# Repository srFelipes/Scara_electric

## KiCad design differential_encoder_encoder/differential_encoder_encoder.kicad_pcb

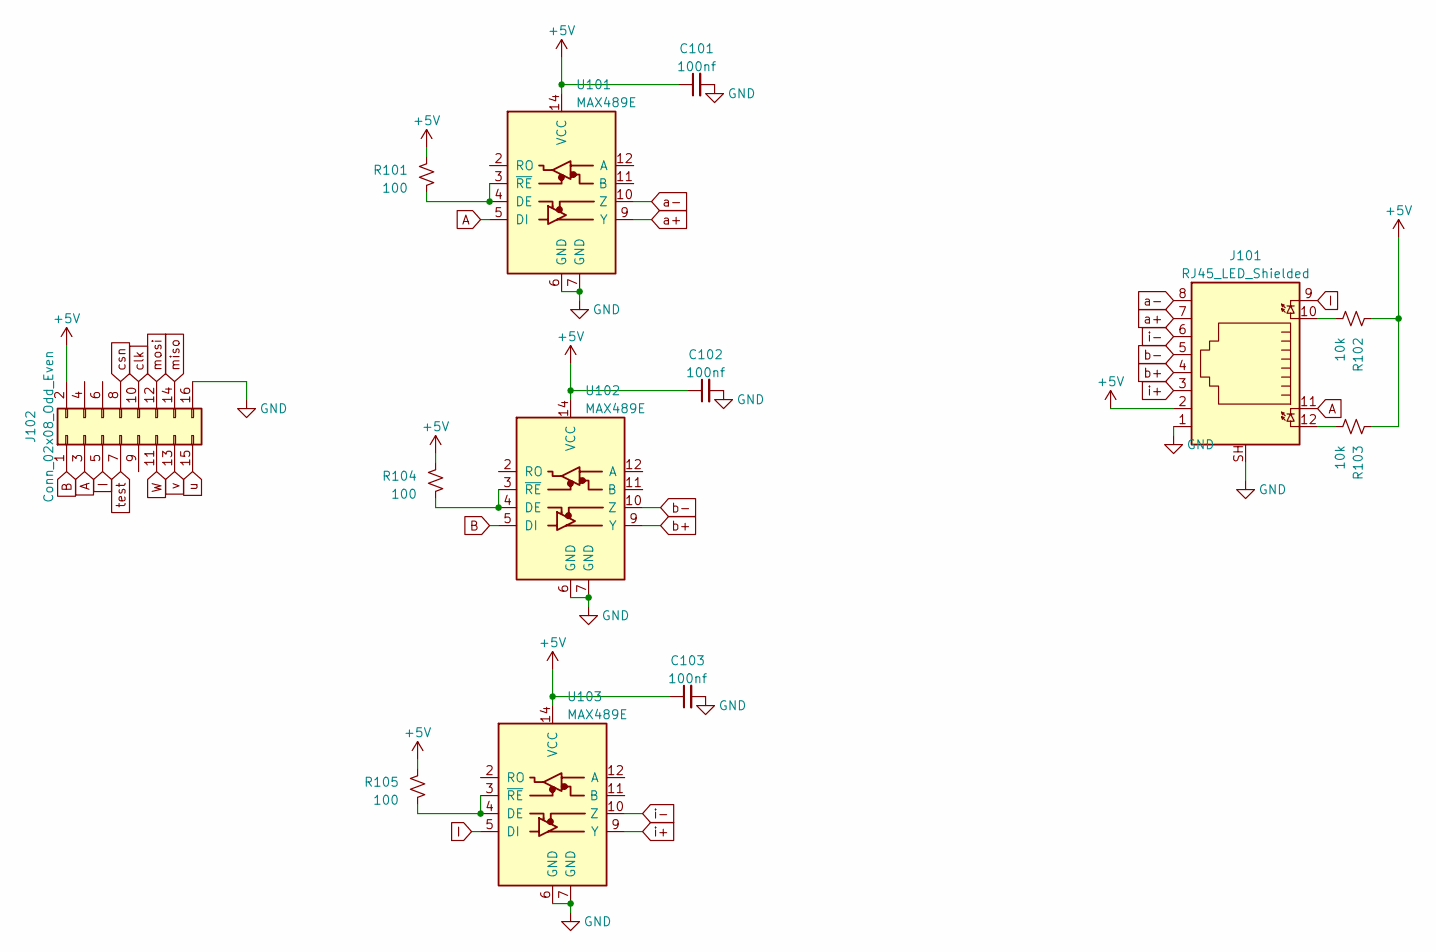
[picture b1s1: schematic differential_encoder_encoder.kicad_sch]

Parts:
C101, C102, C103: 100nf; C_0805_2012Metric_Pad1.18x1.45mm_HandSolder
J101: RJ45_LED_Shielded; RJ45_Amphenol_RJHSE538X
J102: Conn_02x08_Odd_Even; PinSocket_2x08_P2.54mm_Vertical
R101, R104, R105: 100; R_0805_2012Metric_Pad1.20x1.40mm_HandSolder
R102, R103: 10k; R_0805_2012Metric_Pad1.20x1.40mm_HandSolder
U101, U102, U103: MAX489E; SO-14_3.9x8.65mm_P1.27mm

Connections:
+5V: C101.1, C102.1, C103.1, J101.2, J102.2, R101.1, R102.1, R103.1, R104.1, R105.1, U101.14 (VCC), U102.14 (VCC), U103.14 (VCC)
A: J101.11, J102.3, U101.5 (DI)
B: J102.1, U102.5 (DI)
GND: C101.2, C102.2, C103.2, J101.1, J101.SH, J102.16, U101.6 (GND), U101.7 (GND), U102.6 (GND), U102.7 (GND), U103.6 (GND), U103.7 (GND)
I: J101.9, J102.5, U103.5 (DI)
unnamed: J101.10, R102.2
unnamed: J101.12, R103.2
unnamed: R101.2, U101.3 (~RE), U101.4 (DE)
unnamed: R104.2, U102.3 (~RE), U102.4 (DE)
unnamed: R105.2, U103.3 (~RE), U103.4 (DE)
W: J102.11
a+: J101.7, U101.9 (Y)
a-: J101.8, U101.10 (Z)
b+: J101.4, U102.9 (Y)
b-: J101.5, U102.10 (Z)
clk: J102.10
csn: J102.8
i+: J101.3, U103.9 (Y)
i-: J101.6, U103.10 (Z)
miso: J102.14
mosi: J102.12
test: J102.7
u: J102.15
v: J102.13

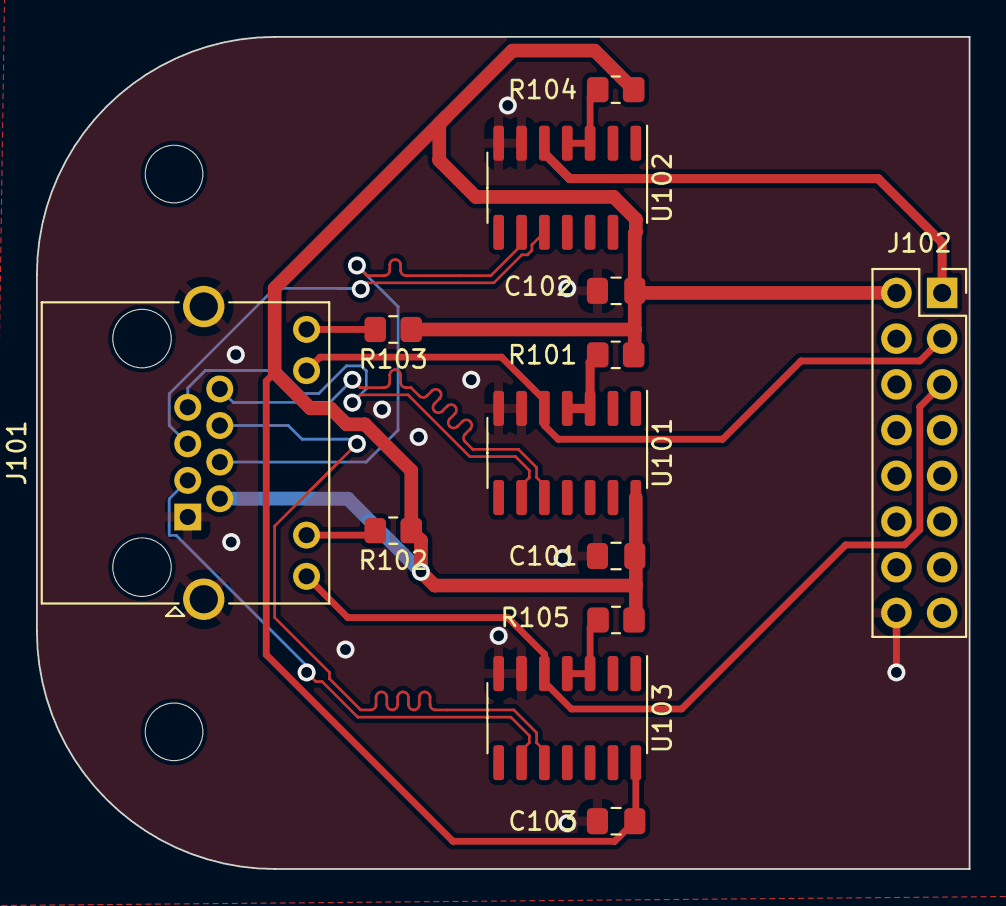
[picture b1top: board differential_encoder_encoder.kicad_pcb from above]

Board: 2 copper layers, 51.8 x 46.2 mm, 13 parts (0 on the bottom side), 16 nets.

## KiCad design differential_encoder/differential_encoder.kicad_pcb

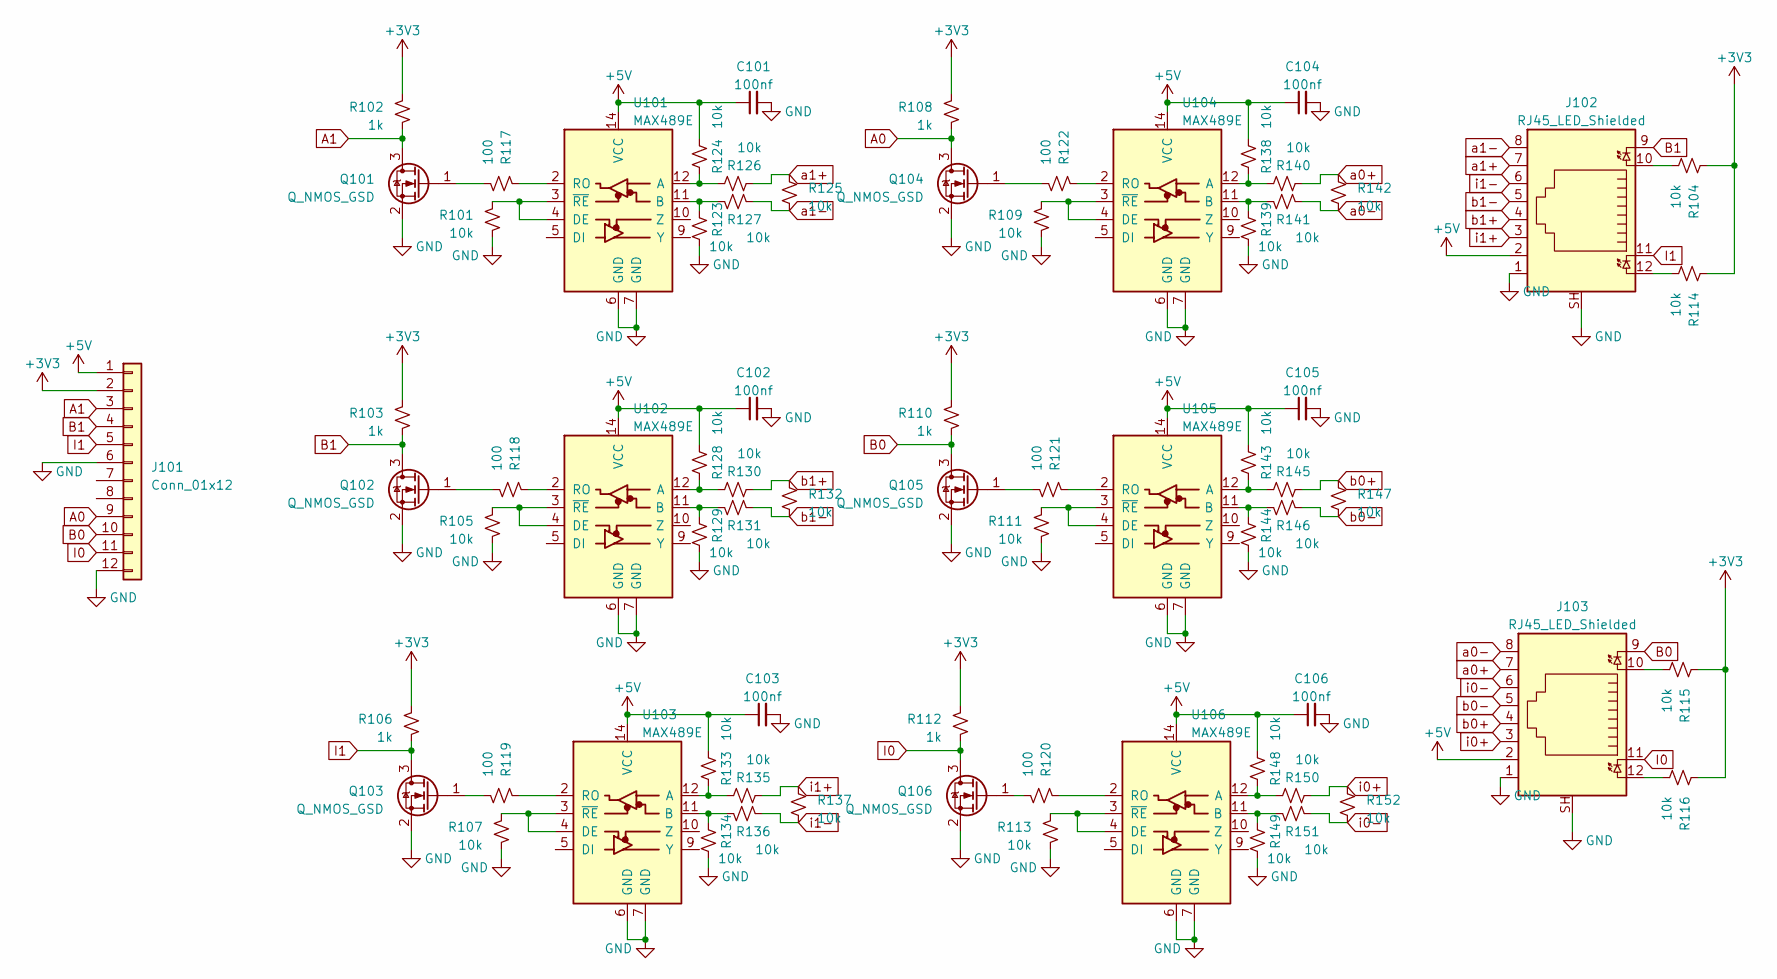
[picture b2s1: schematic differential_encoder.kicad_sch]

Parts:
C101, C102, C103, C104, C105, C106: 100nf; C_0805_2012Metric_Pad1.18x1.45mm_HandSolder
J101: Conn_01x12; PinSocket_1x12_P2.54mm_Vertical
J102, J103: RJ45_LED_Shielded; RJ45_Amphenol_RJHSE538X
Q101, Q102, Q103, Q104, Q105, Q106: Q_NMOS_GSD; SOT-23-3
R101, R104, R105, R107, R109, R111, R113, R114, R115, R116, R123, R124, R125, R126, R127, R128, R129, R130, R131, R132, R133, R134, R135, R136, R137, R138, R139, R140, R141, R142, R143, R144, R145, R146, R147, R148, R149, R150, R151, R152: 10k; R_0805_2012Metric_Pad1.20x1.40mm_HandSolder
R102, R103, R106, R108, R110, R112: 1k; R_0805_2012Metric_Pad1.20x1.40mm_HandSolder
R117, R118, R119, R120, R121, R122: 100; R_0805_2012Metric_Pad1.20x1.40mm_HandSolder
U101, U102, U103, U104, U105, U106: MAX489E; SO-14_3.9x8.65mm_P1.27mm

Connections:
+3V3: J101.2, R102.1, R103.1, R104.1, R106.1, R108.1, R110.1, R112.1, R114.1, R115.1, R116.1
+5V: C101.1, C102.1, C103.1, C104.1, C105.1, C106.1, J101.1, J102.2, J103.2, R124.1, R128.1, R133.1, R138.1, R143.1, R148.1, U101.14 (VCC), U102.14 (VCC), U103.14 (VCC), U104.14 (VCC), U105.14 (VCC), U106.14 (VCC)
A0: J101.9, Q104.3 (D), R108.2
A1: J101.3, Q101.3 (D), R102.2
B0: J101.10, J103.9, Q105.3 (D), R110.2
B1: J101.4, J102.9, Q102.3 (D), R103.2
GND: C101.2, C102.2, C103.2, C104.2, C105.2, C106.2, J101.6, J101.12, J102.1, J102.SH, J103.1, J103.SH, Q101.2 (S), Q102.2 (S), Q103.2 (S), Q104.2 (S), Q105.2 (S), Q106.2 (S), R101.2, R105.2, R107.2, R109.2, R111.2, R113.2, R123.2, R129.2, R134.2, R139.2, R144.2, R149.2, U101.6 (GND), U101.7 (GND), U102.6 (GND), U102.7 (GND), U103.6 (GND), U103.7 (GND), U104.6 (GND), U104.7 (GND), U105.6 (GND), U105.7 (GND), U106.6 (GND), U106.7 (GND)
I0: J101.11, J103.11, Q106.3 (D), R112.2
I1: J101.5, J102.11, Q103.3 (D), R106.2
unnamed: J102.10, R104.2
unnamed: J102.12, R114.2
unnamed: J103.10, R115.2
unnamed: J103.12, R116.2
unnamed: Q101.1 (G), R117.2
unnamed: Q102.1 (G), R118.2
unnamed: Q103.1 (G), R119.2
unnamed: Q104.1 (G), R122.2
unnamed: Q105.1 (G), R121.2
unnamed: Q106.1 (G), R120.2
unnamed: R124.2, R126.1, U101.12 (A)
unnamed: R123.1, R127.1, U101.11 (B)
unnamed: R101.1, U101.3 (~RE), U101.4 (DE)
unnamed: R117.1, U101.2 (RO)
unnamed: R128.2, R130.1, U102.12 (A)
unnamed: R129.1, R131.1, U102.11 (B)
unnamed: R105.1, U102.3 (~RE), U102.4 (DE)
unnamed: R118.1, U102.2 (RO)
unnamed: R133.2, R135.1, U103.12 (A)
unnamed: R134.1, R136.1, U103.11 (B)
unnamed: R107.1, U103.3 (~RE), U103.4 (DE)
unnamed: R119.1, U103.2 (RO)
unnamed: R138.2, R140.1, U104.12 (A)
unnamed: R139.1, R141.1, U104.11 (B)
unnamed: R109.1, U104.3 (~RE), U104.4 (DE)
unnamed: R122.1, U104.2 (RO)
unnamed: R143.2, R145.1, U105.12 (A)
unnamed: R144.1, R146.1, U105.11 (B)
unnamed: R111.1, U105.3 (~RE), U105.4 (DE)
unnamed: R121.1, U105.2 (RO)
unnamed: R148.2, R150.1, U106.12 (A)
unnamed: R149.1, R151.1, U106.11 (B)
unnamed: R113.1, U106.3 (~RE), U106.4 (DE)
unnamed: R120.1, U106.2 (RO)
a0+: J103.7, R140.2, R142.1
a0-: J103.8, R141.2, R142.2
a1+: J102.7, R125.1, R126.2
a1-: J102.8, R125.2, R127.2
b0+: J103.4, R145.2, R147.1
b0-: J103.5, R146.2, R147.2
b1+: J102.4, R130.2, R132.1
b1-: J102.5, R131.2, R132.2
i0+: J103.3, R150.2, R152.1
i0-: J103.6, R151.2, R152.2
i1+: J102.3, R135.2, R137.1
i1-: J102.6, R136.2, R137.2

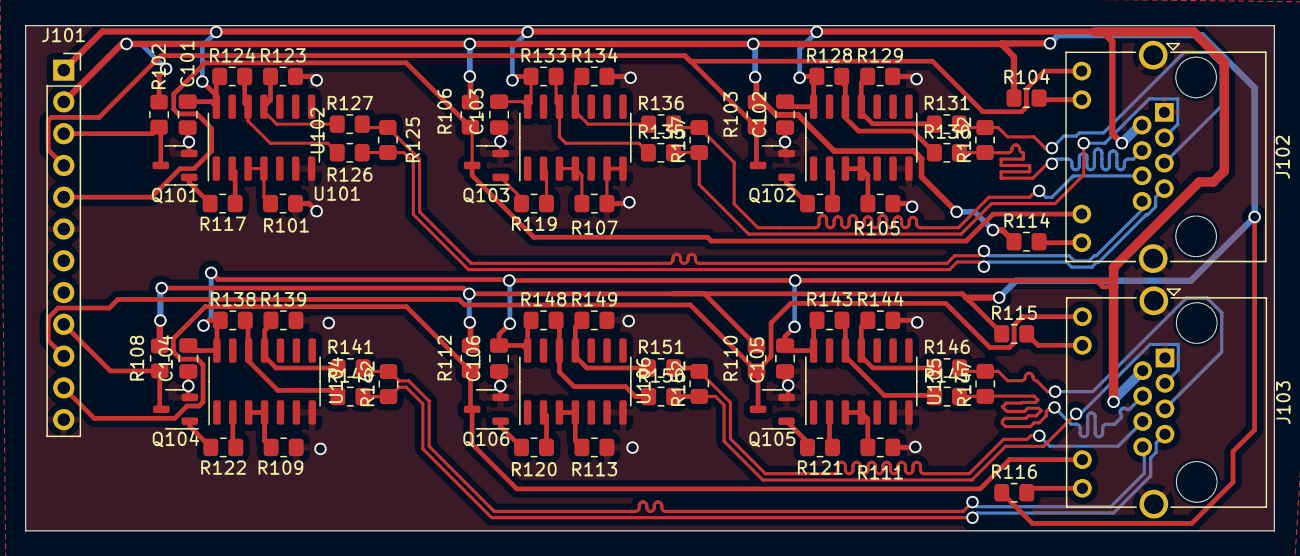
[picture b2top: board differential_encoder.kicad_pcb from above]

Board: 2 copper layers, 99.8 x 40.4 mm, 73 parts (0 on the bottom side), 55 nets.

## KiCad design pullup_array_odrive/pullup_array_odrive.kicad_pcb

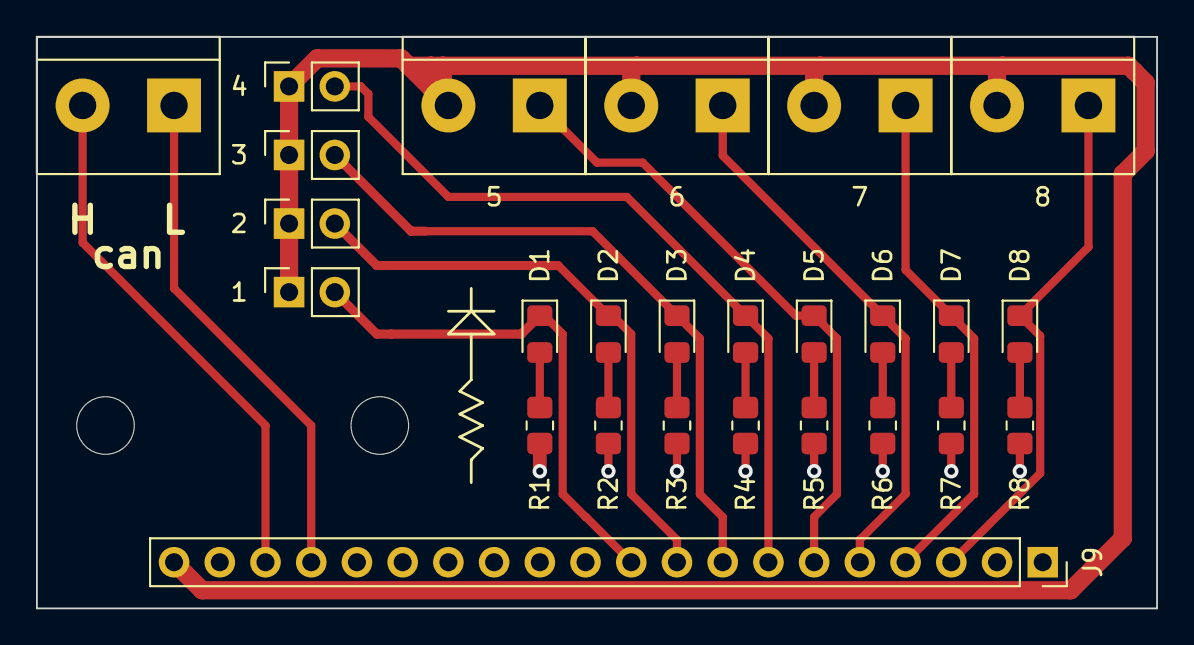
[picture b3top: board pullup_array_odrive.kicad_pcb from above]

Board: 2 copper layers, 62.2 x 31.7 mm, 26 parts (0 on the bottom side), 20 nets.

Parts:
1, 2, 3, 4: 2.54mm header; PinSocket_1x02_P2.54mm_Vertical
5, 6, 7, 8: 2.54mm header; TerminalBlock_bornier-2_P5.08mm
CAN1: 2.54mm header; TerminalBlock_bornier-2_P5.08mm
D1, D2, D3, D4, D5, D6, D7, D8: R; D_0805_2012Metric_Pad1.15x1.40mm_HandSolder
J9: Conn_01x20_Male; PinSocket_1x20_P2.54mm_Vertical
R1, R2, R3, R4, R5, R6, R7, R8: 1k; R_0805_2012Metric_Pad1.20x1.40mm_HandSolder

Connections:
+3V3: 1.1, 2.1, 3.1, 4.1, 5.2, 6.2, 7.2, 8.2, J9.20
GND: J9.1, J9.2, J9.16, J9.19, R1.2, R2.2, R3.2, R4.2, R5.2, R6.2, R7.2, R8.2
unnamed: CAN1.1, J9.17
unnamed: CAN1.2, J9.18
unnamed: 1.2, D1.1 (K), J9.10
unnamed: D1.2 (A), R1.1
unnamed: 2.2, D2.1 (K), J9.9
unnamed: D2.2 (A), R2.1
unnamed: 3.2, D3.1 (K), J9.8
unnamed: D3.2 (A), R3.1
unnamed: 4.2, D4.1 (K), J9.7
unnamed: D4.2 (A), R4.1
unnamed: 5.1, D5.1 (K), J9.6
unnamed: D5.2 (A), R5.1
unnamed: 6.1, D6.1 (K), J9.5
unnamed: D6.2 (A), R6.1
unnamed: 7.1, D7.1 (K), J9.4
unnamed: D7.2 (A), R7.1
unnamed: 8.1, D8.1 (K), J9.3
unnamed: D8.2 (A), R8.1

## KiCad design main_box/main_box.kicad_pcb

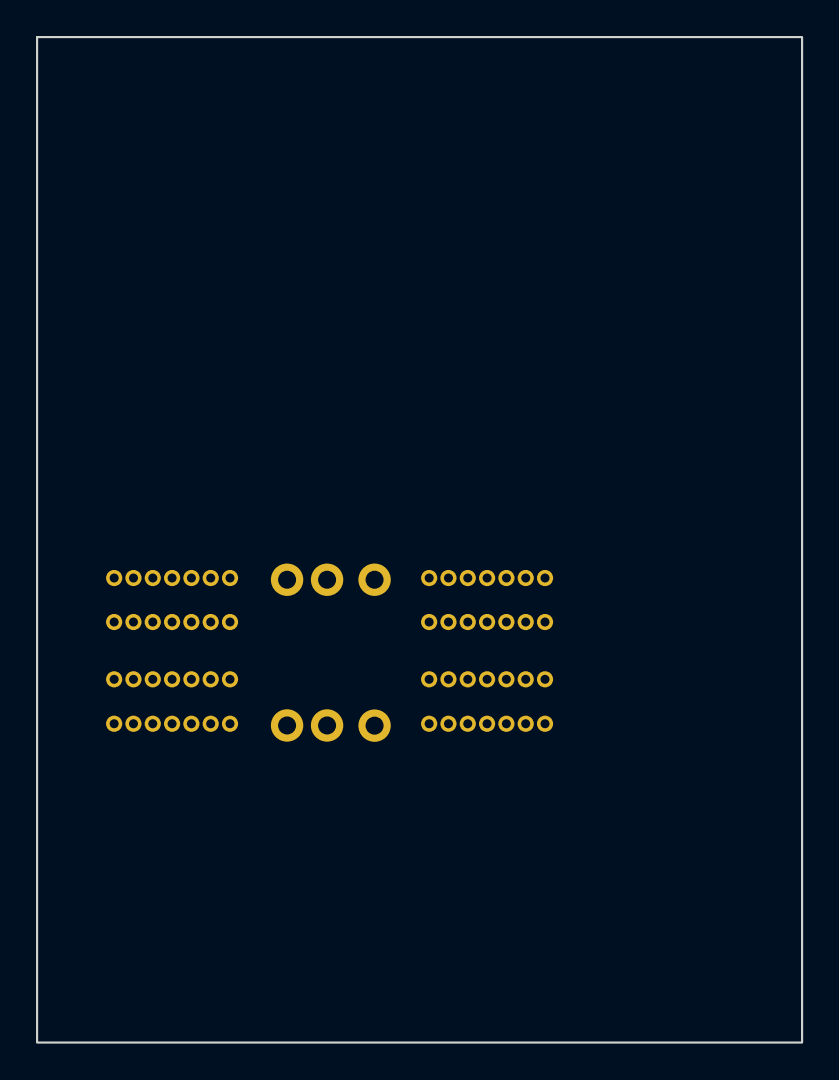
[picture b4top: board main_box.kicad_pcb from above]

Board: 2 copper layers, 42.5 x 55.9 mm, 4 parts (0 on the bottom side), 3 nets, no tracks yet.

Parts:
CB1: CircuitBreaker_1P; interruptor_1p_scale_1to8
CB2: differential_2P; interruptor_2p_scale_1to8
DB1, DB2: distribution_block_4_bars_04x07_scale_1to8

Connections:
GND: DB2.15, DB2.22
L0: CB1.1, DB1.1
unnamed: CB1.2, CB2.1

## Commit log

2022-04-16 created proyect for main box
2022-04-18 Added 5v pówer supply for independent raspberry pi power, modified the switchgear topology
2022-04-18 added odrive to electronic devices
2022-04-30 created gitignore file
2022-05-05 created extension board for limit switches and can bus
2023-06-14 last changes
2023-06-15 finished encoder pcb
2023-06-15 tentative odrive positioning
2023-06-16 first odrive board
2023-06-17 finished odrive layout
2023-06-18 final version odrive
2023-06-19 new encoder layout
2023-06-26 added ignores
2023-06-27 encoder traces are now chonkers
2023-06-27 odrive traces are now chunky
2023-06-27 finished the encoder tracing
